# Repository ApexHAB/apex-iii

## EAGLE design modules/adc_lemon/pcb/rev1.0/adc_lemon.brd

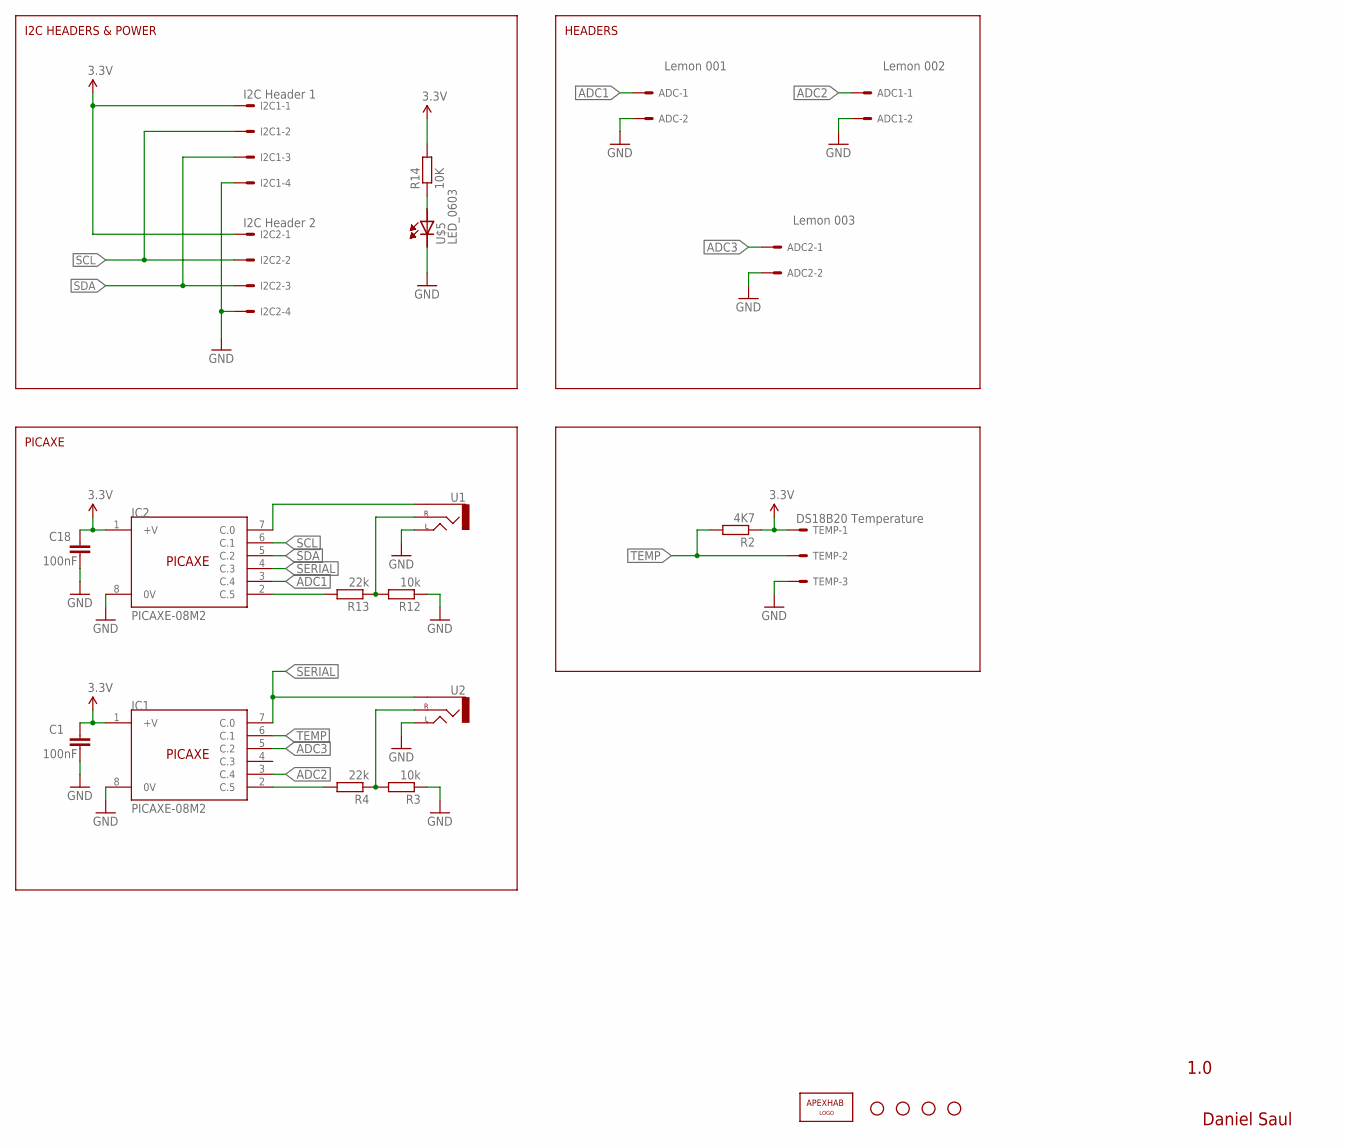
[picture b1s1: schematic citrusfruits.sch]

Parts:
ADC: Lemon 001; 6410-02
ADC1: Lemon 002; 6410-02
ADC2: Lemon 003; 6410-02
C1, C18: 100nF; C0805
I2C1: I2C Header 1; 6410-04
I2C2: I2C Header 2; 6410-04
IC1, IC2: PICAXE-08M2; SOIC8
JP1: APEXHAB-LOGO_APEXHAB-SMALL; APEXHAB-LOGO-SMALL
JP2, JP3, JP4, JP5: STAND-OFF
R2: 4K7; R0805
R3, R12: 10k; R0805
R4, R13: 22k; R0805
R14: 10K; R0805
TEMP: DS18B20 Temperature; 6410-03
U1, U2: AUDIO-JACKPTH; AUDIO-JACK
U$5: LED_0603; CHIPLED_0603

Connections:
3.3V: C1.1, C18.1, I2C1.1, I2C2.1, IC1.1 (+V), IC2.1 (+V), R2.1, R14.2, TEMP.1
ADC1: ADC.1, IC2.3 (C.4)
ADC2: ADC1.1, IC1.3 (C.4)
ADC3: ADC2.1, IC1.5 (C.2)
GND: ADC.2, ADC1.2, ADC2.2, C1.2, C18.2, I2C1.4, I2C2.4, IC1.8 (0V), IC2.8 (0V), R3.1, R12.1, TEMP.3, U1.TIP (LEFT), U2.TIP (LEFT), U$5.C
unnamed: IC1.2 (C.5), R4.2
unnamed: R3.2, R4.1, U2.RING (RIGHT)
unnamed: IC2.2 (C.5), R13.2
unnamed: IC2.7 (C.0), U1.SLEEVE
unnamed: R12.2, R13.1, U1.RING (RIGHT)
unnamed: R14.1, U$5.A
SCL: I2C1.2, I2C2.2, IC2.6 (C.1)
SDA: I2C1.3, I2C2.3, IC2.5 (C.2)
SERIAL: IC1.7 (C.0), IC2.4 (C.3), U2.SLEEVE
TEMP: IC1.6 (C.1), R2.2, TEMP.2

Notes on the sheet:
1.0
Daniel Saul
I2C HEADERS & POWER
HEADERS
PICAXE

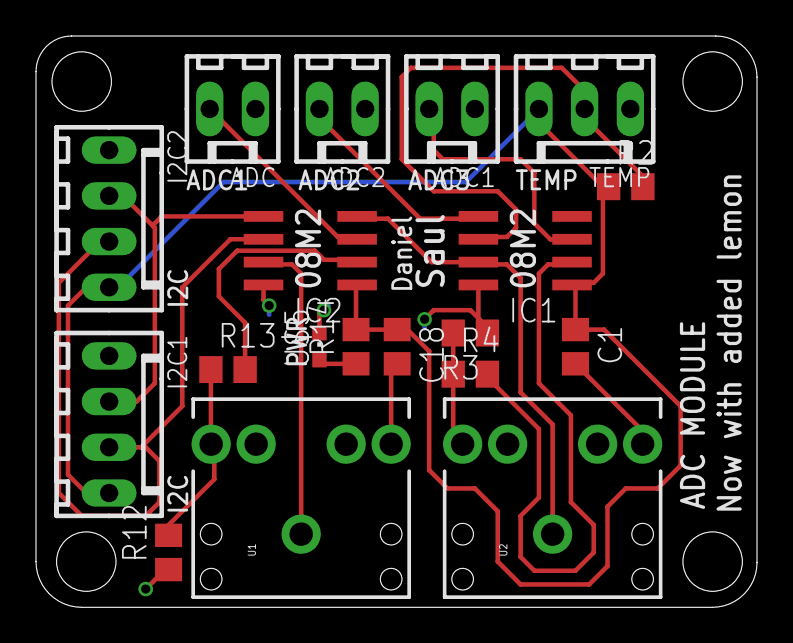
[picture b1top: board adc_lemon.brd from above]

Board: 2 copper layers, 40.1 x 31.7 mm, 24 parts (1 on the bottom side), 15 nets.
